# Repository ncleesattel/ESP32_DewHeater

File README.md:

# ESP32_DewHeater
Dew heater using the MyDewHeater from Robert Brown as starting point to understand circutry and software.

## Hardware Features
* Integration in Bopla Alubos case equal in size to the TeenAstro Main Unit.
* Design comprised of 3x pcbs
   * main dew heater circutry
   * connection panel top
   * sensor panel bottom
* Design uses SMDs to make use of the JLCPCB assembly service.

### Power Distribution
* Breakout DC-power jacks for
   * TeenAstro Main Unit
   * Intel NUC or Lenovo ThinkCentre
   * AstroCam
   * Filter-Rotator
### Dew Heater
* 3-Channel output that can be used for dew straps or a flat-field light.
* Use of high efficiency MOSFETs to eliminate need for heat sink.
* Integration of current and voltage sensors to calculate actual power output.
* Use of BME280 sensor to calculate dew point.
* Use of rotary pulse encoders to adjust power output.

## Software Features
* Bare knuckle software without closed-loop shenanigans.
* Read sensors and rotary pulse encoders.
* Calculate power output and dew point.
* Adjust output with enoder input only.

## BOM
What do you need for this build.
* dew_control_pcb
* dew_connector_pcb
* dew_sensor_pcb
* OLED 2.42" from DIYMORE configured to I2C or similar
* ESP32 30-pin MCU
* Bopla Alubos ABPH-1300-0150 bottom half
* 3D print for top cover which also fits display
* 3D print of side cover connector
* 3D print of side cover sensor
* 2x Mentor aluminum knobs 521.611
* 3x RCA connector Cliff FC68375
* 8x DC-jack Cliff FC681445 (5.5mm x 2.1mm type)
* 6x JST VH VHR-2N connectors for 3 cables
* 3x JST VH B2P-VH (LF) connector to solder to pcbs
* TE Mate N Lok 350211-1 connector to solder to pcb
* Marquart Series 1800 switch (on/off)
* Ruthex M2.5 threaded inserts

## Cost estimate
| Item | Number | Cost |
|-----|-----|-----|
| dew_control_pcb | 5 | 160|
| dew_sensor_pcb | 5 | 15|
| dew_connector_pcb | 5 | 15|
| ESP32 30-in MCU | 1 | 10|
| OLED 2.42 | 1 | 20|
| BOPLA Alubos ABPH 1300-0150 | 1 | 50|
| Cliff RCA connectors | 3 | 10 |
| Cliff DC jacks | 8 | 24 |
| various other | x | 20 |

Best case 170 Eur if you can share all pcbs  
Worst case 320 Eur if you keep all pcbs and build only one

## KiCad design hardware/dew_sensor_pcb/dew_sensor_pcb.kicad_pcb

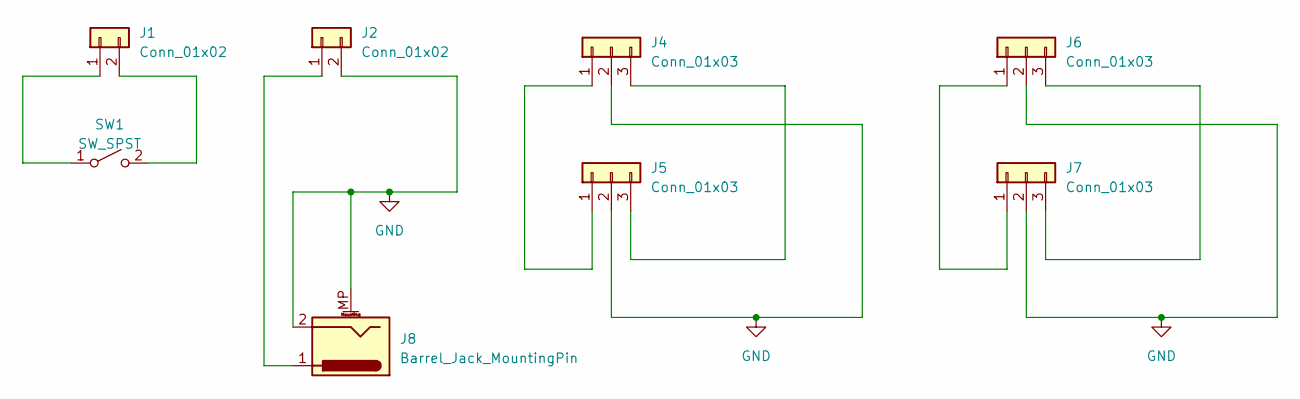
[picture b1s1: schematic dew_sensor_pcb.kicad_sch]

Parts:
J1, J2: Conn_01x02; JST_VH_B2P-VH-B_1x02_P3.96mm_Vertical
J4, J6: Conn_01x03; JST_XH_B3B-XH-A_1x03_P2.50mm_Vertical
J5, J7: Conn_01x03; PinHeader_1x03_P2.54mm_Vertical
J8: Barrel_Jack_MountingPin; BarrelJack_Vertical
SW1: SW_SPST; Marquart

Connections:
GND: J2.2, J4.2, J5.2, J6.2, J7.2, J8.2, J8.MP (MountPin)
unnamed: J1.1, SW1.1 (A)
unnamed: J1.2, SW1.2 (B)
unnamed: J2.1, J8.1
unnamed: J4.1, J5.1
unnamed: J4.3, J5.3
unnamed: J6.1, J7.1
unnamed: J6.3, J7.3

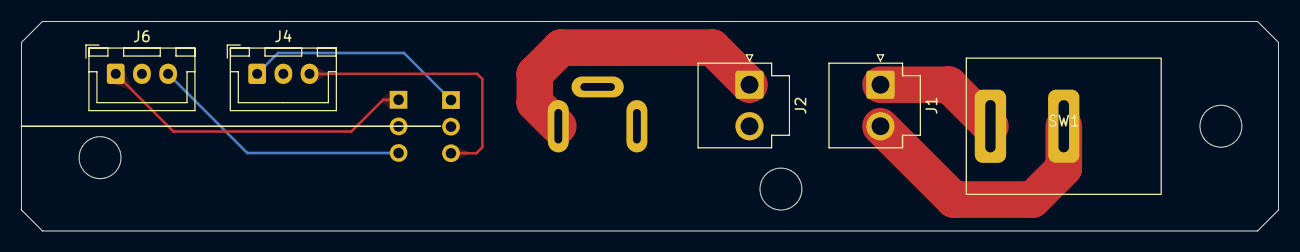
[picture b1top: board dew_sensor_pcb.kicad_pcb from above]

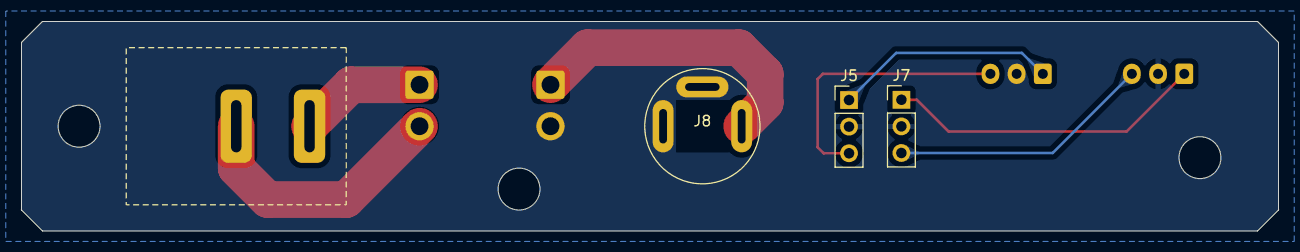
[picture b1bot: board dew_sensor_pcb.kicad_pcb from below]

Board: 2 copper layers, 120.0 x 20.0 mm, 8 parts (3 on the bottom side), 8 nets.

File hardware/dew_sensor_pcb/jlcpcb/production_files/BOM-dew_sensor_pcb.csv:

Comment,Designator,Footprint,LCSC
Conn_01x03,J7,PinHeader_1x03_P2.54mm_Vertical,
Conn_01x02,J1,JST_VH_B2P-VH-B_1x02_P3.96mm_Vertical,
Conn_01x02,J2,JST_VH_B2P-VH-B_1x02_P3.96mm_Vertical,
SW_SPST,SW1,Marquart,
Conn_01x03,J4,JST_XH_B3B-XH-A_1x03_P2.50mm_Vertical,
Conn_01x03,J6,JST_XH_B3B-XH-A_1x03_P2.50mm_Vertical,
Conn_01x03,J5,PinHeader_1x03_P2.54mm_Vertical,
Barrel_Jack_MountingPin,J8,BarrelJack_Vertical,

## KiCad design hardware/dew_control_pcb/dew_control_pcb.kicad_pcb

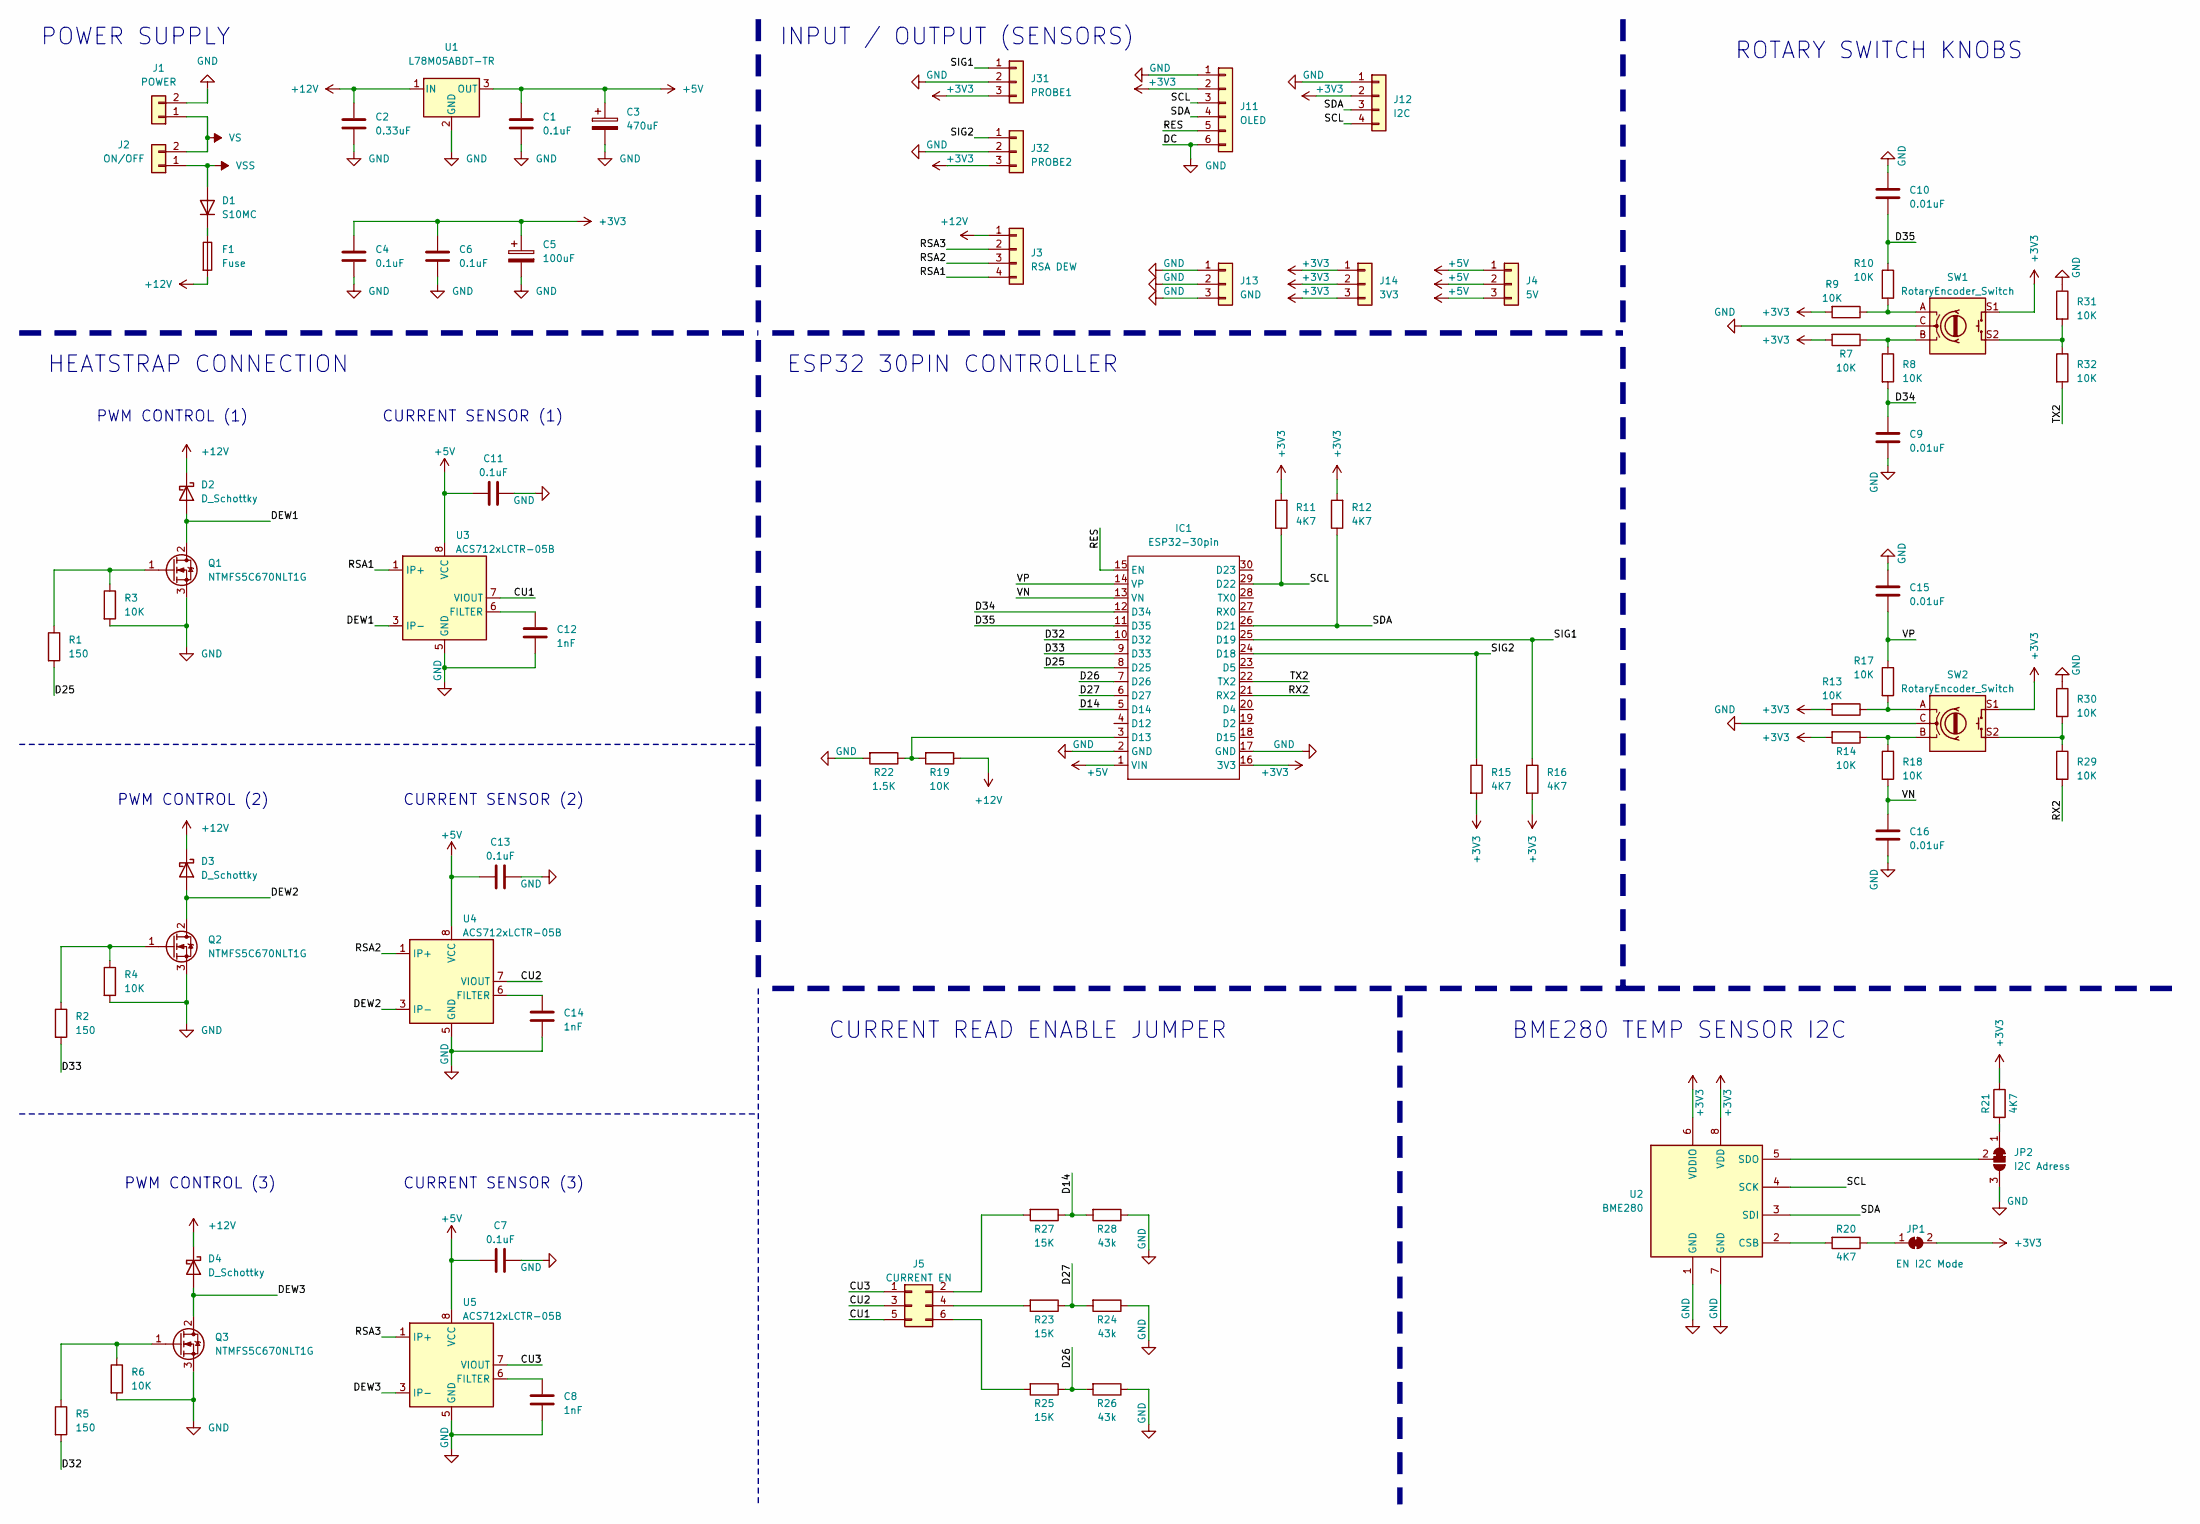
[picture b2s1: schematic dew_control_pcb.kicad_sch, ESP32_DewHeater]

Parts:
C1, C4, C6, C7, C11, C13: 0.1uF; C_0603_1608Metric; LCSC C14663
C2: 0.33uF; C_0603_1608Metric; LCSC C1615
C3: 470uF; C_Elec_10x10.2; LCSC C72518
C5: 100uF; C_Elec_10x10.2; LCSC C280414
C8, C12, C14: 1nF; C_0603_1608Metric; LCSC C8808
C9, C10, C15, C16: 0.01uF; C_0805_2012Metric; LCSC C376921
D1: S10MC; D_SMC; LCSC C169472
D2, D3, D4: D_Schottky; D_SMA; JLCPCB C8678
F1: Fuse; Fuseholder_Cylinder-5x20mm; LCSC C206887
IC1: ESP32-30pin
J1: POWER; JST_VH_S2P-VH_1x02_P3.96mm_Horizontal; LCSC C160355
J2: ON/OFF; JST_VH_S2P-VH_1x02_P3.96mm_Horizontal; LCSC C160355
J3: RSA DEW; TE_MATE-N-LOK_1x04_P5.08mm_Horizontal; LCSC C492552
J4: 5V; PinHeader_1x03_P2.54mm_Vertical
J5: CURRENT EN; PinHeader_2x03_P2.54mm_Horizontal; LCSC C239334
J11: OLED; JST_XH_S6B-XH-A_1x06_P2.50mm_Horizontal; LCSC C157919
J12: I2C; PinHeader_1x04_P2.54mm_Horizontal; LCSC C293357
J13: GND; PinHeader_1x03_P2.54mm_Vertical
J14: 3V3; PinHeader_1x03_P2.54mm_Vertical
J31: PROBE1; PinHeader_1x03_P2.54mm_Horizontal; LCSC C706866
J32: PROBE2; PinHeader_1x03_P2.54mm_Horizontal; LCSC C706866
JP1: EN I2C Mode; SolderJumper-2_P1.3mm_Bridged_RoundedPad1.0x1.5mm
JP2: I2C Adress; SolderJumper-3_P1.3mm_Bridged12_RoundedPad1.0x1.5mm
Q1, Q2, Q3: NTMFS5C670NLT1G; ONSemi_SO-8FL_488AA; LCSC C179626
R1, R2, R5: 150; R_0603_1608Metric; LCSC C22808
R3, R4, R6, R7, R8, R9, R10, R13, R14, R17, R18, R19, R29, R30, R31, R32: 10K; R_0603_1608Metric; LCSC C25804
R11, R12, R15, R16, R20, R21: 4K7; R_0603_1608Metric; LCSC C23162
R22: 1.5K; R_1206_3216Metric; LCSC C26036
R23, R25, R27: 15K; R_0603_1608Metric; LCSC C22809
R24, R26, R28: 43k; R_0603_1608Metric; LCSC C23172
SW1, SW2: RotaryEncoder_Switch; RotaryEncoder_Alps_EC11E-Switch_Vertical_H20mm; LCSC C470754
U1: L78M05ABDT-TR; TO-252-2; LCSC C58069
U2: BME280; Bosch_LGA-8_2.5x2.5mm_P0.65mm_ClockwisePinNumbering; LCSC C92489
U3, U4, U5: ACS712xLCTR-05B; SOIC-8_3.9x4.9mm_P1.27mm; LCSC C44471

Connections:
+3V3: C4.1, C5.1, C6.1, IC1.16 (3V3), J11.2, J12.2, J14.1, J14.2, J14.3, J31.3, J32.3, JP1.2 (B), R7.2, R9.2, R11.2, R12.2, R13.2, R14.2, R15.2, R16.2, R21.1, SW1.S1, SW2.S1, U2.6 (VDDIO), U2.8 (VDD)
+5V: C1.1, C3.1, C7.1, C11.1, C13.1, IC1.1 (VIN), J4.1, J4.2, J4.3, U1.3 (OUT), U3.8 (VCC), U4.8 (VCC), U5.8 (VCC)
+12V: C2.1, D2.1 (K), D3.1 (K), D4.1 (K), F1.2, J3.1, R19.1, U1.1 (IN)
/CU1: J5.5, U3.7 (VIOUT)
/CU2: J5.3, U4.7 (VIOUT)
/CU3: J5.1, U5.7 (VIOUT)
/D14: IC1.5 (D14), R27.1, R28.2
/D25: IC1.8 (D25), R1.2
/D26: IC1.7 (D26), R25.1, R26.2
/D27: IC1.6 (D27), R23.1, R24.2
/D32: IC1.10 (D32), R5.2
/D33: IC1.9 (D33), R2.2
/D34: C9.1, IC1.12 (D34), R8.2
/D35: C10.2, IC1.11 (D35), R10.1
/DEW1: D2.2 (A), Q1.2 (D), U3.3 (IP-), U3.4 (IP-)
/DEW2: D3.2 (A), Q2.2 (D), U4.3 (IP-), U4.4 (IP-)
/DEW3: D4.2 (A), Q3.2 (D), U5.3 (IP-), U5.4 (IP-)
/RES: IC1.15 (EN), J11.5
/RSA1: J3.4, U3.1 (IP+), U3.2 (IP+)
/RSA2: J3.3, U4.1 (IP+), U4.2 (IP+)
/RSA3: J3.2, U5.1 (IP+), U5.2 (IP+)
/RX2: IC1.21 (RX2), R29.2
/SCL: IC1.29 (D22), J11.3, J12.4, R11.1, U2.4 (SCK)
/SDA: IC1.26 (D21), J11.4, J12.3, R12.1, U2.3 (SDI)
/SIG1: IC1.25 (D19), J31.1, R16.1
/SIG2: IC1.24 (D18), J32.1, R15.1
/TX2: IC1.22 (TX2), R32.2
/VN: C16.1, IC1.13 (VN), R18.2
/VP: C15.2, IC1.14 (VP), R17.1
GND: C1.2, C2.2, C3.2, C4.2, C5.2, C6.2, C7.2, C8.1, C9.2, C10.1, C11.2, C12.1, C13.2, C14.1, C15.1, C16.2, IC1.2 (GND), IC1.17 (GND), J1.2, J11.1, J11.6, J12.1, J13.1, J13.2, J13.3, J31.2, J32.2, JP2.3 (B), Q1.3 (S), Q2.3 (S), Q3.3 (S), R3.2, R4.2, R6.2, R22.2, R24.1, R26.1, R28.1, R30.1, R31.1, SW1.C, SW2.C, U1.2 (GND), U2.1 (GND), U2.7 (GND), U3.5 (GND), U4.5 (GND), U5.5 (GND)
unnamed: D1.1 (K), F1.1
unnamed: IC1.3 (D13), R19.2, R22.1
unnamed: J5.2, R27.2
unnamed: J5.4, R23.2
unnamed: J5.6, R25.2
unnamed: JP1.1 (A), R20.1
unnamed: JP2.1 (A), R21.2
unnamed: JP2.2 (C), U2.5 (SDO)
unnamed: Q1.1 (G), R1.1, R3.1
unnamed: Q2.1 (G), R2.1, R4.1
unnamed: Q3.1 (G), R5.1, R6.1
unnamed: R7.1, R8.1, SW1.B
unnamed: R9.1, R10.2, SW1.A
unnamed: R13.1, R17.2, SW2.A
unnamed: R14.1, R18.1, SW2.B
unnamed: R29.1, R30.2, SW2.S2
unnamed: R31.2, R32.1, SW1.S2
unnamed: R20.2, U2.2 (CSB)
unnamed: C12.2, U3.6 (FILTER)
unnamed: C14.2, U4.6 (FILTER)
unnamed: C8.2, U5.6 (FILTER)
VS: J1.1, J2.2
VSS: D1.2 (A), J2.1

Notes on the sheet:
PWM CONTROL (2)
INPUT / OUTPUT (SENSORS)
PWM CONTROL (1)
HEATSTRAP CONNECTION
ESP32 30PIN CONTROLLER
CURRENT SENSOR (1)
ROTARY SWITCH KNOBS
BME280 TEMP SENSOR I2C
CURRENT SENSOR (2)
CURRENT SENSOR (3)
PWM CONTROL (3)
CURRENT READ ENABLE JUMPER
POWER SUPPLY

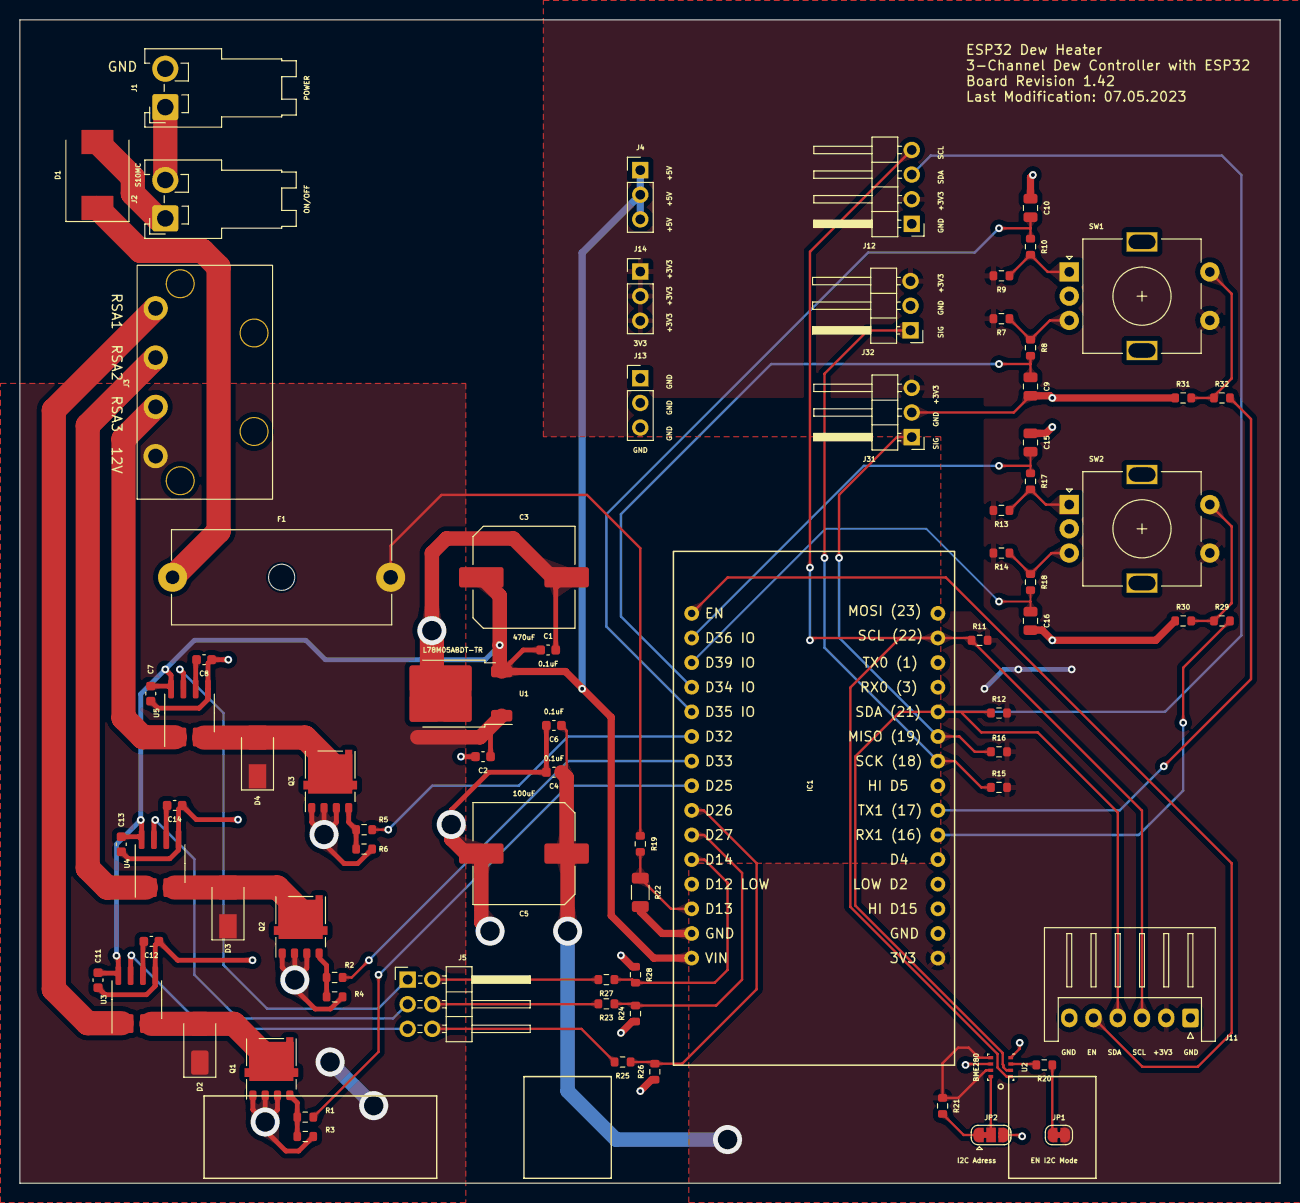
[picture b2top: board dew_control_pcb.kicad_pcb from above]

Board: 2 copper layers, 130.0 x 120.0 mm, 77 parts (0 on the bottom side), 53 nets.

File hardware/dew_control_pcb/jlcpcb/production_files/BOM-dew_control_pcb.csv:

Comment,Designator,Footprint,LCSC
0.1uF,"C1,C11,C13,C4,C6,C7",C_0603_1608Metric,C14663
OLED,J11,JST_XH_S6B-XH-A_1x06_P2.50mm_Horizontal,C157919
POWER,"J1,J2",JST_VH_S2P-VH_1x02_P3.96mm_Horizontal,C160355
0.33uF,C2,C_0603_1608Metric,C1615
S10MC,D1,D_SMC,C169472
NTMFS5C670NLT1G,"Q1,Q2,Q3",ONSemi_SO-8FL_488AA,C179626
Fuse,F1,Fuseholder_Cylinder-5x20mm,C206887
150,"R1,R2,R5",R_0603_1608Metric,C22808
15K,"R23,R25,R27",R_0603_1608Metric,C22809
4K7,"R11,R12,R15,R16,R20,R21",R_0603_1608Metric,C23162
43k,"R24,R26,R28",R_0603_1608Metric,C23172
CURRENT EN,J5,PinHeader_2x03_P2.54mm_Horizontal,C239334
10K,"R10,R13,R14,R17,R18,R19,R29,R3,R30,R31,R32,R4,R6,R7,R8,R9",R_0603_1608Metric,C25804
1.5K,R22,R_1206_3216Metric,C26036
100uF,C5,C_Elec_10x10.2,C280414
I2C,J12,PinHeader_1x04_P2.54mm_Horizontal,C293357
0.01uF,"C10,C15,C16,C9",C_0805_2012Metric,C376921
ACS712xLCTR-05B,"U3,U4,U5",SOIC-8_3.9x4.9mm_P1.27mm,C44471
RotaryEncoder_Switch,"SW1,SW2",RotaryEncoder_Alps_EC11E-Switch_Vertical_H20mm,C470754
RSA DEW,J3,TE_MATE-N-LOK_1x04_P5.08mm_Horizontal,C492552
L78M05ABDT-TR,U1,TO-252-2,C58069
PROBE1,"J31,J32",PinHeader_1x03_P2.54mm_Horizontal,C706866
470uF,C3,C_Elec_10x10.2,C72518
D_Schottky,"D2,D3,D4",D_SMA,C8678
1nF,"C12,C14,C8",C_0603_1608Metric,C8808
BME280,U2,Bosch_LGA-8_2.5x2.5mm_P0.65mm_ClockwisePinNumbering,C92489
I2C Adress,JP2,SolderJumper-3_P1.3mm_Bridged12_RoundedPad1.0x1.5mm,
3V3,J14,PinHeader_1x03_P2.54mm_Vertical,
GND,J13,PinHeader_1x03_P2.54mm_Vertical,
ESP32-30pin,IC1,ESP32-30pin,
5V,J4,PinHeader_1x03_P2.54mm_Vertical,
EN I2C Mode,JP1,SolderJumper-2_P1.3mm_Bridged_RoundedPad1.0x1.5mm,

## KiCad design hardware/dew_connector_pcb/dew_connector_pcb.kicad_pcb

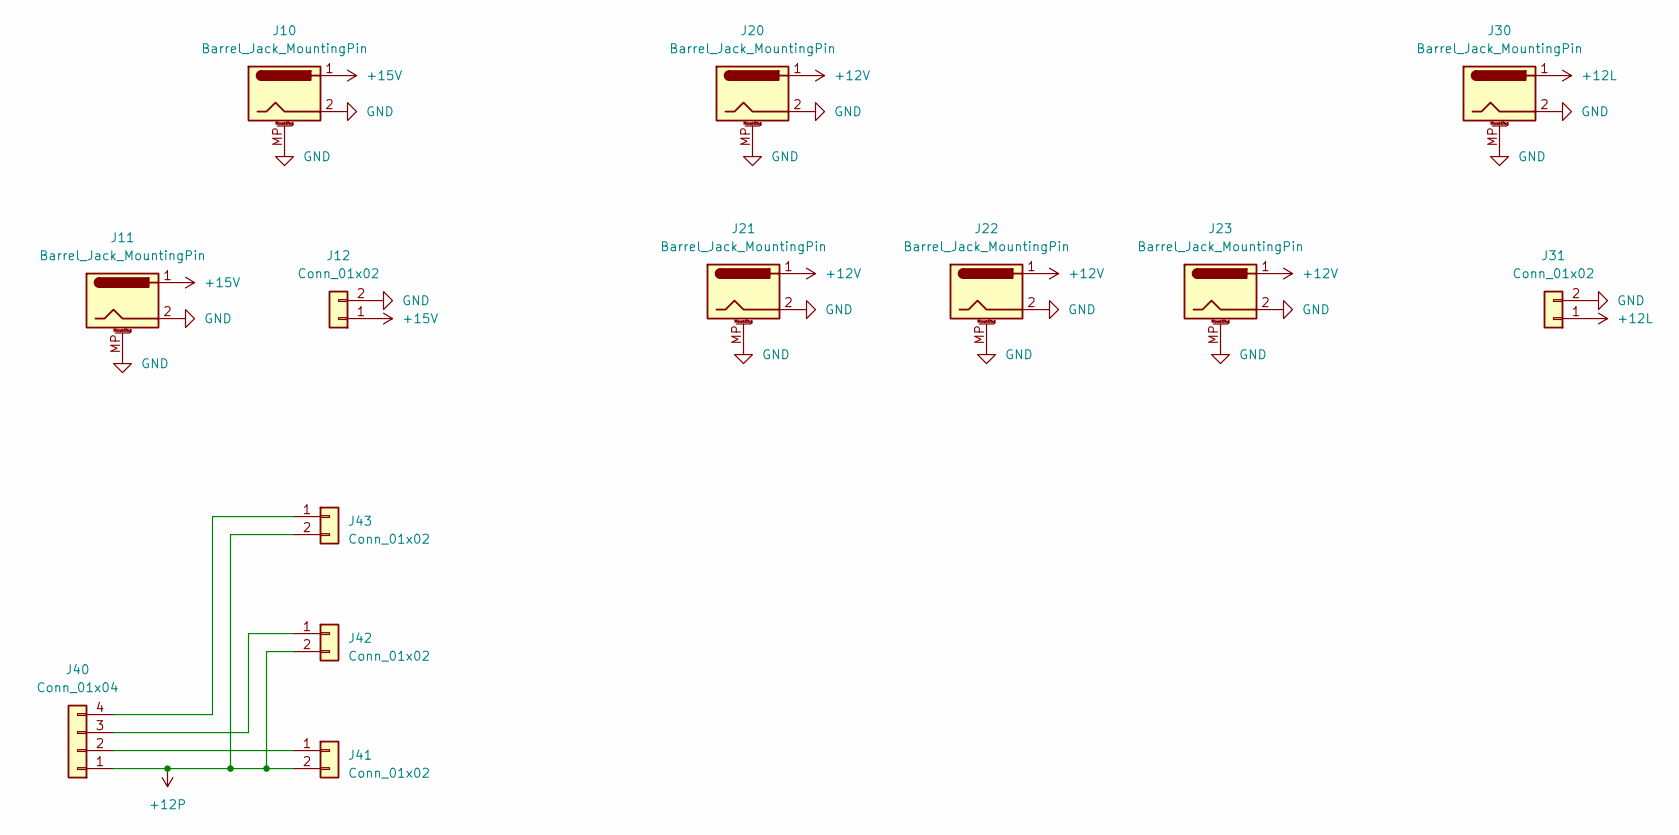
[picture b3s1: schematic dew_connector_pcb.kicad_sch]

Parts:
J10, J11, J20, J21, J22, J23, J30: Barrel_Jack_MountingPin; BarrelJack_Vertical
J12, J31: Conn_01x02; JST_VH_B2P-VH_1x02_P3.96mm_Vertical
J40: Conn_01x04; TE_MATE-N-LOK_350211-1_1x04_P5.08mm_Vertical
J41, J42, J43: Conn_01x02; Cinch_Vertical

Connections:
+12L: J30.1, J31.1
+12P: J40.1, J41.2, J42.2, J43.2
+12V: J20.1, J21.1, J22.1, J23.1
+15V: J10.1, J11.1, J12.1
GND: J10.2, J10.MP (MountPin), J11.2, J11.MP (MountPin), J12.2, J20.2, J20.MP (MountPin), J21.2, J21.MP (MountPin), J22.2, J22.MP (MountPin), J23.2, J23.MP (MountPin), J30.2, J30.MP (MountPin), J31.2
unnamed: J40.2, J41.1
unnamed: J40.3, J42.1
unnamed: J40.4, J43.1

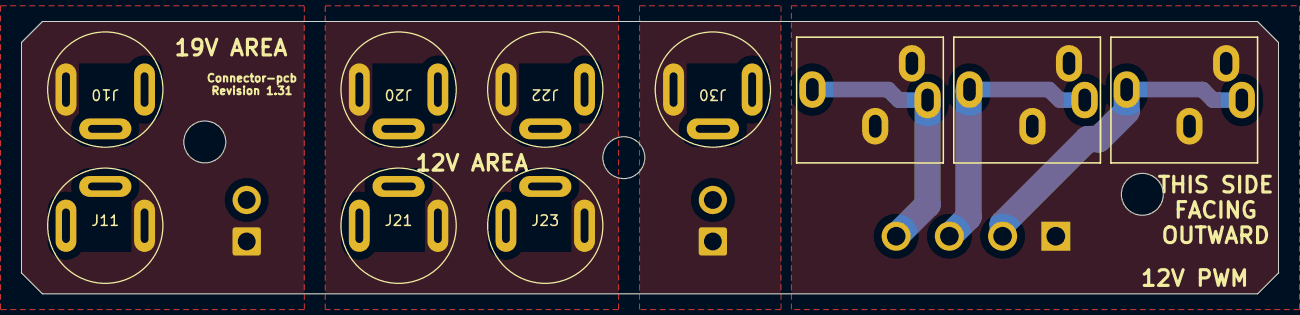
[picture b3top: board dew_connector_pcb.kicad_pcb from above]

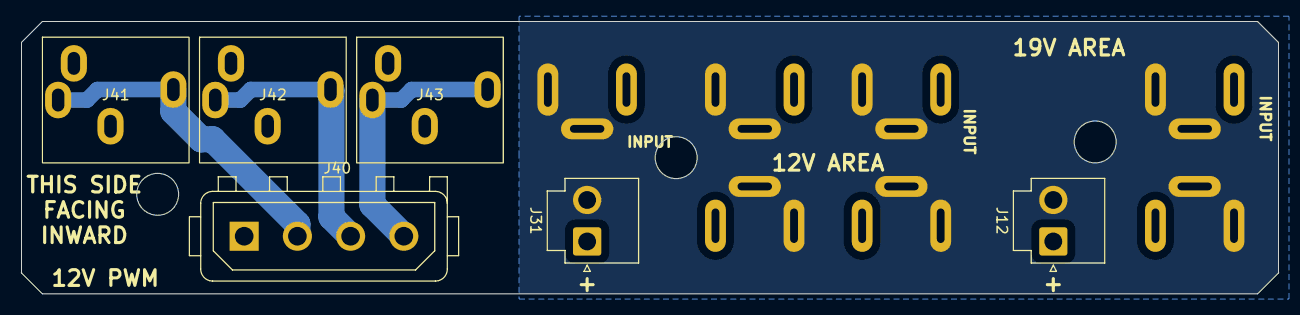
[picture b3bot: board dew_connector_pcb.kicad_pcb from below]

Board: 2 copper layers, 120.0 x 26.0 mm, 13 parts (6 on the bottom side), 8 nets.

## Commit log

2023-09-16 Initial Setup
2023-09-16 Create LICENSE
2023-09-24 Add pictures
2023-09-24 Add dew connector pcb
2023-09-24 Add dew control pcb
2023-09-24 Add dew sensor pcb
